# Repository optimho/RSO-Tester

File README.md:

# RSO-Tester
Repetitive Surge generator for testing generator rotors 

This circuit is used to provide a steep fronted pulse.
See the instruction manual for information about how to use this device to detect inter-turn faults in a generator rotor.

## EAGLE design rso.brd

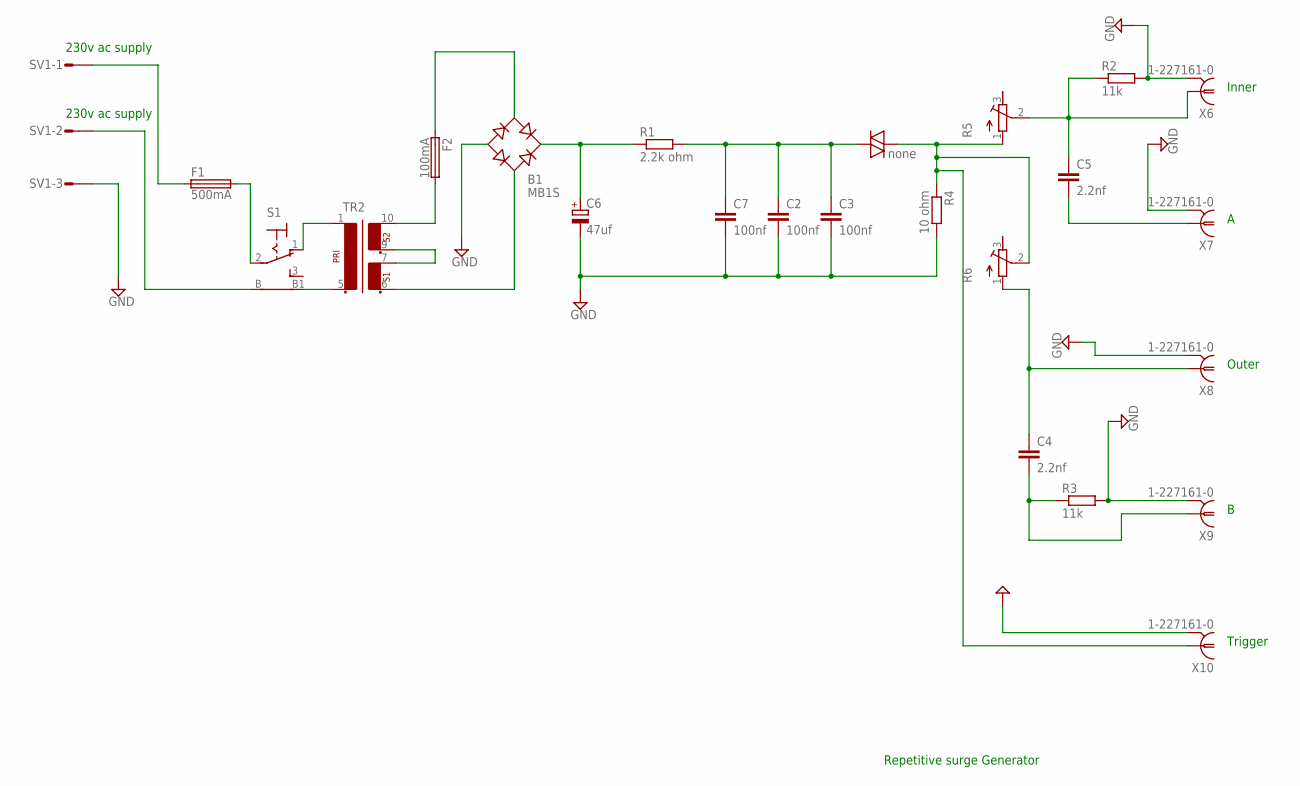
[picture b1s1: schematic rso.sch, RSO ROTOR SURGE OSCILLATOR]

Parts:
B1: MB1S; SOIC-4; MPN MB1S
C2, C3, C7: 100nf; C0805; MPN 08055C104KAZ2A
C4, C5: 2.2nf; C0805; MPN 04025C222JAT2A
C6: 47uf; 140CLH-1010; MPN EEEFK1K470P
D1: none; DO35-10; MPN NTE6408
F1: 500mA; SH22,5A; MPN C0345RAAAA
F2: 100mA; SH22,5A; MPN C0345RAAAA
R1: 2.2k ohm; R2512W; MPN CRCW08052K20FKEA
R2, R3: 11k; M0805; MPN MCMR08X1102FTL
R4: 10 ohm; M0805; MPN CRT1206-BY-10R0ELF
R5, R6: R-TRIMM3339P; RTRIM3339P; MPN 534B1101JL
S1: LPV-1; MPN 761-18/003
SV1: L03P; MPN B03B-XASK-1(LF)(SN)
TR2: EI38-2; MPN 44203
X6, X7, X8, X9, X10: 1-227161-0; AMP_227161; MPN 1-1337542-0

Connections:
GND: B1.-, C2.2, C3.2, C6.-, C7.2, R2.2, R3.2, R4.2, SV1.3, X6.2, X7.2, X8.2, X9.2, X10.2
unnamed: B1.~1 (AC1), F2.1
unnamed: B1.~2 (AC2), TR2.6 (3)
unnamed: TR2.7 (4), TR2.9 (5)
unnamed: S1.B, SV1.2
unnamed: F1.1, SV1.1
unnamed: F1.2, S1.2
unnamed: S1.B1, TR2.5 (2)
unnamed: S1.1 (O), TR2.1
unnamed: B1.+, C6.+, R1.1
unnamed: C4.2, R3.1, X9.1
unnamed: C2.1, C3.1, C7.1, D1.A (1), R1.2
unnamed: D1.C (2), R4.1, R5.1 (A), R6.2 (S), X10.1
unnamed: C4.1, R6.1 (A), X8.1
unnamed: C5.1, R2.1, R5.2 (S), X6.1
unnamed: C5.2, X7.1
unnamed: F2.2, TR2.10 (6)

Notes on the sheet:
230v ac supply
Trigger
Inner
Outer
Repetitive surge Generator

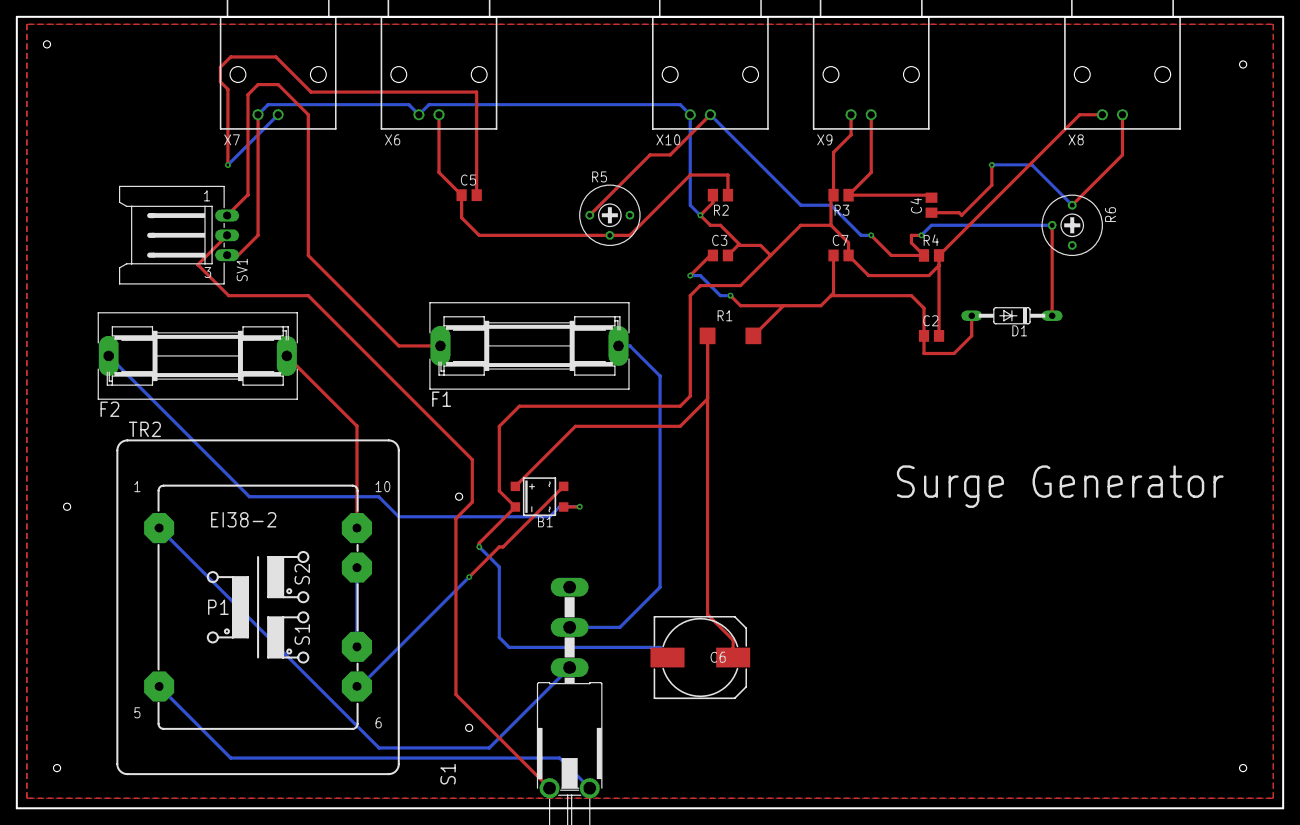
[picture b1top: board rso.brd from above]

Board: 2 copper layers, 160.0 x 100.0 mm, 24 parts (0 on the bottom side), 17 nets.

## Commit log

2019-08-25 RSO Test Set
2019-08-25 CHanges to the thikness of the tracks
2019-08-25 Remove old bom csv
2019-08-25 Update the Gerber Files
2019-09-03 Add instruction manual
2019-09-03 Add Paper by P.G.S Kumar
2019-09-03 Additional Literature for RSO
